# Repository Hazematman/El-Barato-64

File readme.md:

# El Barato 64
Open source N64 development cartridge. Currently a WIP
- Hardware is currently untested
- firmware still needs to be written for board

Uses Altera MAX II EPM570 to emulate N64 cartridge bus. N64 ROM is stored in SDRAM controlled by this FPGA. Uses an STM32 for USB communication and general board control.
This board is designed to be as cheap as possible and beginner friendly. Parts were selected based on their avaliablity in the JLCPCB part inventory. All components except the micro USB connector and reset switch are avalible from JLCPCB, and thus they can manufacture the majority of the board.

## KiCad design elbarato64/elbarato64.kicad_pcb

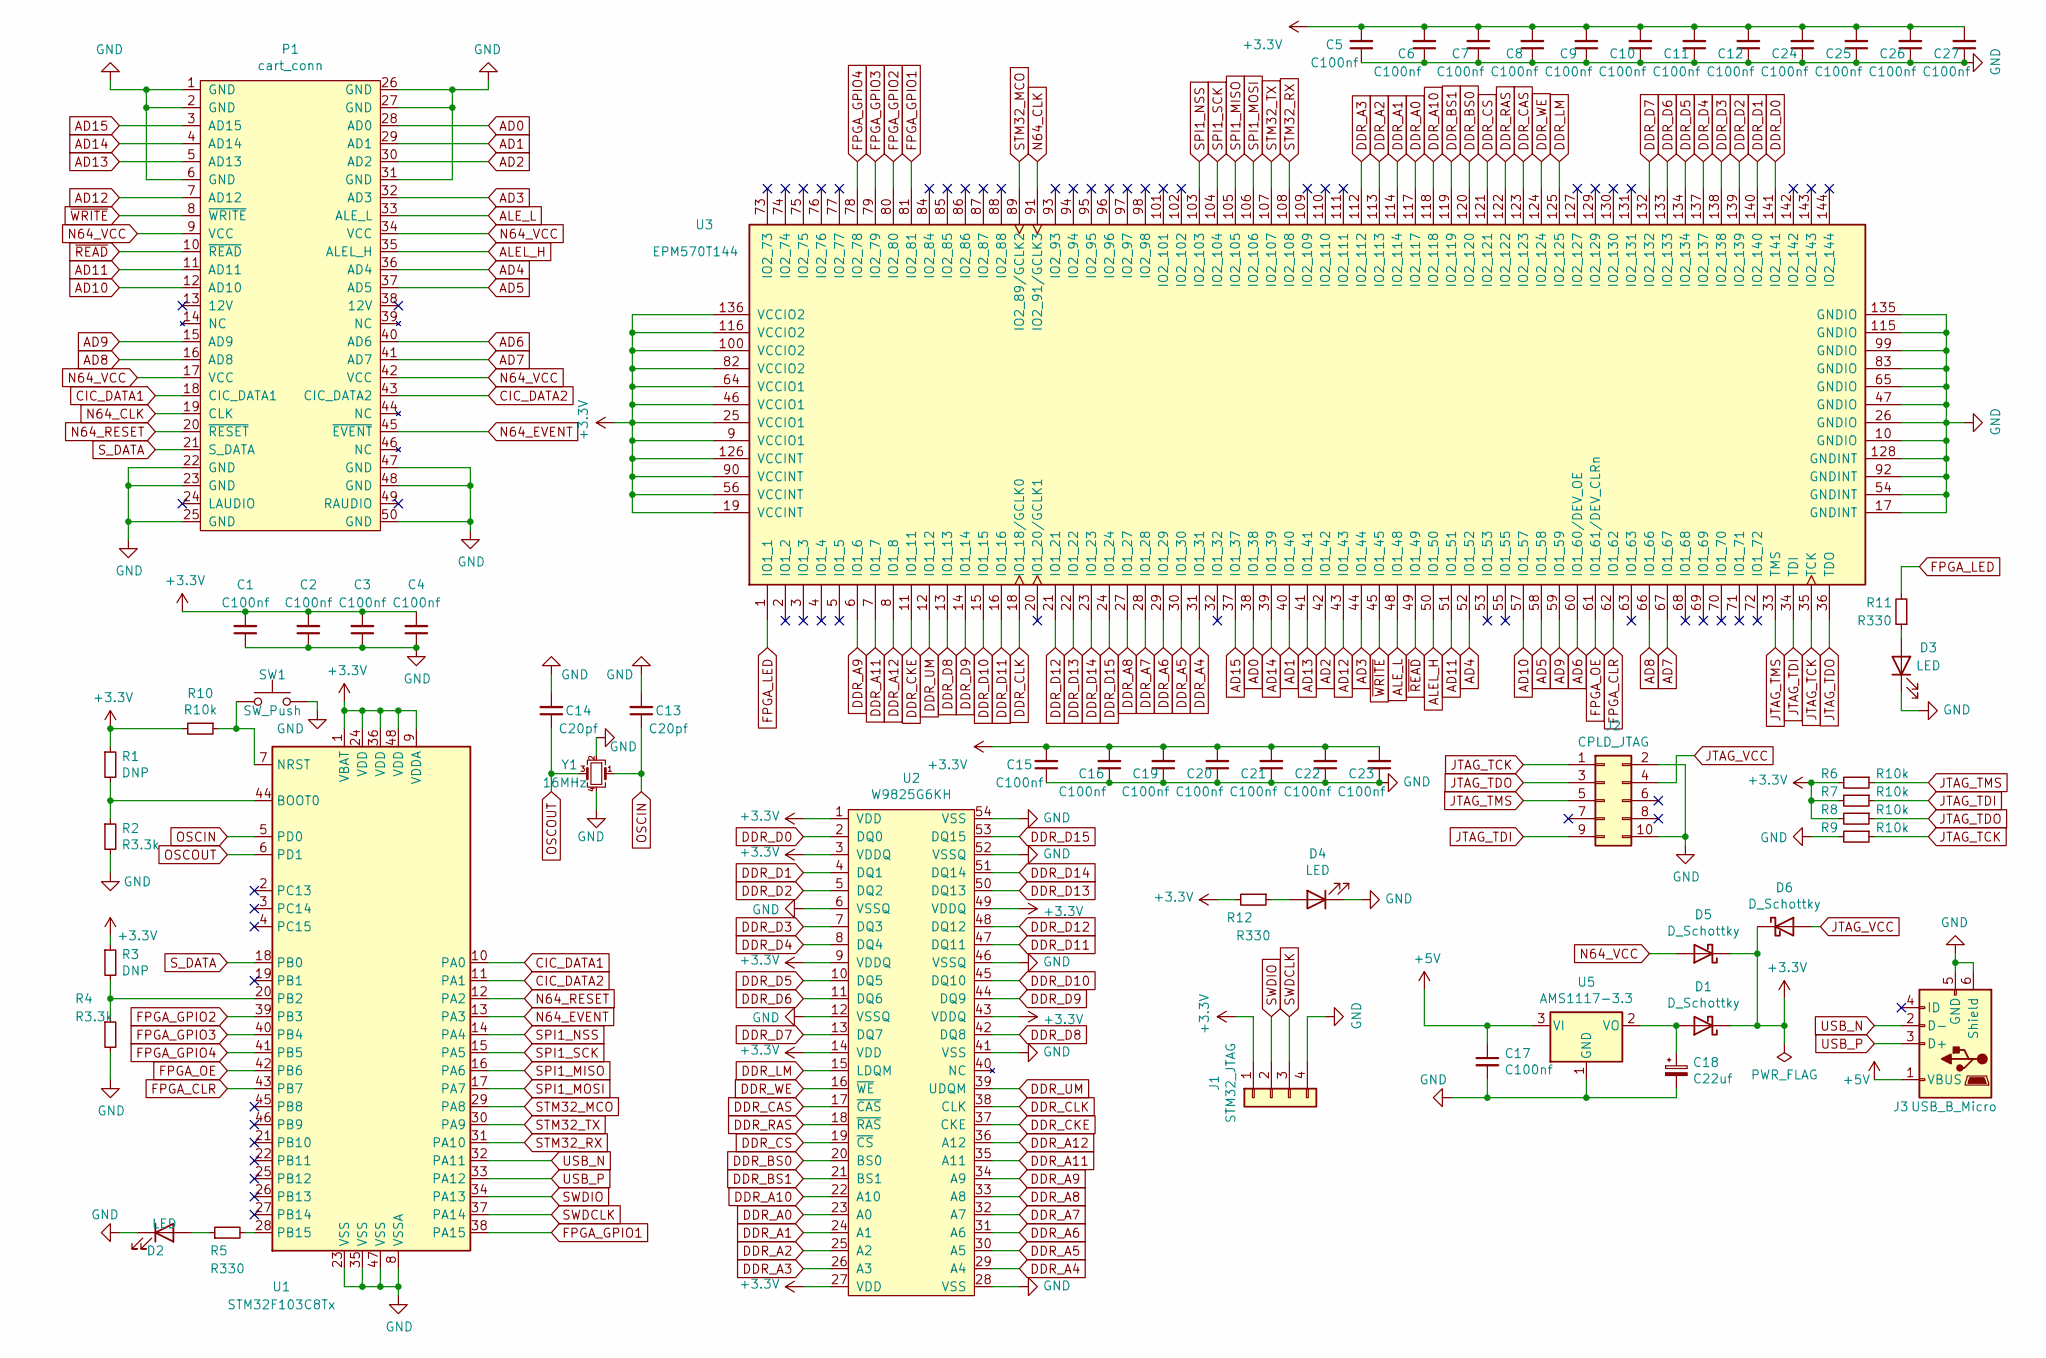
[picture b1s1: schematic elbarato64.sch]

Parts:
C1, C2, C3, C4, C5, C6, C7, C8, C9, C10, C11, C12, C15, C16, C17, C19, C20, C21, C22, C23, C24, C25, C26, C27: C100nf; C_0603_1608Metric_Pad1.05x0.95mm_HandSolder
C13, C14: C20pf; C_0603_1608Metric_Pad1.05x0.95mm_HandSolder
C18: C22uf; C_0603_1608Metric_Pad1.05x0.95mm_HandSolder
D1, D5, D6: D_Schottky; D_SOD-123
D2, D3, D4: LED; LED_0603_1608Metric_Pad1.05x0.95mm_HandSolder
J1: STM32_JTAG; PinHeader_1x04_P2.54mm_Vertical
J2: CPLD_JTAG; PinHeader_2x05_P2.54mm_Vertical
J3: USB_B_Micro; USB_Micro-AB_Molex_47590-0001
P1: cart_conn; Conn_N64
R1, R3: DNP; R_0603_1608Metric_Pad1.05x0.95mm_HandSolder
R2, R4: R3.3k; R_0603_1608Metric_Pad1.05x0.95mm_HandSolder
R5, R11, R12: R330; R_0603_1608Metric_Pad1.05x0.95mm_HandSolder
R6, R7, R8, R9, R10: R10k; R_0603_1608Metric_Pad1.05x0.95mm_HandSolder
SW1: SW_Push; SW_PUSH_6mm
U1: STM32F103C8Tx; LQFP-48_7x7mm_P0.5mm
U2: W9825G6KH; TSOP-II-54_22.2x10.16mm_P0.8mm
U3: EPM570T144; LQFP-144_20x20mm_P0.5mm
U5: AMS1117-3.3; SOT-223-3_TabPin2
Y1: 16MHz; Crystal_SMD_3225-4Pin_3.2x2.5mm_HandSoldering

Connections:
+3V3: C1.2, C2.2, C3.2, C4.2, C5.2, C6.2, C7.2, C8.2, C9.2, C10.2, C11.2, C12.2, C15.2, C16.2, C19.2, C20.2, C21.2, C22.2, C23.2, C24.2, C25.2, C26.2, C27.2, D1.1 (K), D5.1 (K), D6.1 (K), J1.1, R1.1, R3.1, R6.2, R7.2, R8.2, R10.2, R12.2, U1.1 (VBAT), U1.9 (VDDA), U1.24 (VDD), U1.36 (VDD), U1.48 (VDD), U2.1 (VDD), U2.3 (VDDQ), U2.9 (VDDQ), U2.14 (VDD), U2.27 (VDD), U2.43 (VDDQ), U2.49 (VDDQ), U3.9 (VCCIO1), U3.19 (VCCINT), U3.25 (VCCIO1), U3.46 (VCCIO1), U3.56 (VCCINT), U3.64 (VCCIO1), U3.82 (VCCIO2), U3.90 (VCCINT), U3.100 (VCCIO2), U3.116 (VCCIO2), U3.126 (VCCINT), U3.136 (VCCIO2)
+5V: C17.1, J3.1 (VBUS), U5.3 (VI)
AD0: P1.28 (AD0), U3.38 (IO1_38)
AD1: P1.29 (AD1), U3.40 (IO1_40)
AD2: P1.30 (AD2), U3.42 (IO1_42)
AD3: P1.32 (AD3), U3.44 (IO1_44)
AD4: P1.36 (AD4), U3.52 (IO1_52)
AD5: P1.37 (AD5), U3.58 (IO1_58)
AD6: P1.40 (AD6), U3.60 (IO1_60/DEV_OE)
AD7: P1.41 (AD7), U3.67 (IO1_67)
AD8: P1.16 (AD8), U3.66 (IO1_66)
AD9: P1.15 (AD9), U3.59 (IO1_59)
AD10: P1.12 (AD10), U3.57 (IO1_57)
AD11: P1.11 (AD11), U3.51 (IO1_51)
AD12: P1.7 (AD12), U3.43 (IO1_43)
AD13: P1.5 (AD13), U3.41 (IO1_41)
AD14: P1.4 (AD14), U3.39 (IO1_39)
AD15: P1.3 (AD15), U3.37 (IO1_37)
ALEL_H: P1.35 (ALEL_H), U3.50 (IO1_50)
ALE_L: P1.33 (ALE_L), U3.48 (IO1_48)
CIC_DATA1: P1.18 (CIC_DATA1), U1.10 (PA0)
CIC_DATA2: P1.43 (CIC_DATA2), U1.11 (PA1)
DDR_A0: U2.23 (A0), U3.117 (IO2_117)
DDR_A1: U2.24 (A1), U3.114 (IO2_114)
DDR_A2: U2.25 (A2), U3.113 (IO2_113)
DDR_A3: U2.26 (A3), U3.112 (IO2_112)
DDR_A4: U2.29 (A4), U3.31 (IO1_31)
DDR_A5: U2.30 (A5), U3.30 (IO1_30)
DDR_A6: U2.31 (A6), U3.29 (IO1_29)
DDR_A7: U2.32 (A7), U3.28 (IO1_28)
DDR_A8: U2.33 (A8), U3.27 (IO1_27)
DDR_A9: U2.34 (A9), U3.6 (IO1_6)
DDR_A10: U2.22 (A10), U3.118 (IO2_118)
DDR_A11: U2.35 (A11), U3.7 (IO1_7)
DDR_A12: U2.36 (A12), U3.8 (IO1_8)
DDR_BS0: U2.20 (BS0), U3.120 (IO2_120)
DDR_BS1: U2.21 (BS1), U3.119 (IO2_119)
DDR_CAS: U2.17 (~CAS), U3.123 (IO2_123)
DDR_CKE: U2.37 (CKE), U3.11 (IO1_11)
DDR_CLK: U2.38 (CLK), U3.18 (IO1_18/GCLK0)
DDR_CS: U2.19 (~CS), U3.121 (IO2_121)
DDR_D0: U2.2 (DQ0), U3.141 (IO2_141)
DDR_D1: U2.4 (DQ1), U3.140 (IO2_140)
DDR_D2: U2.5 (DQ2), U3.139 (IO2_139)
DDR_D3: U2.7 (DQ3), U3.138 (IO2_138)
DDR_D4: U2.8 (DQ4), U3.137 (IO2_137)
DDR_D5: U2.10 (DQ5), U3.134 (IO2_134)
DDR_D6: U2.11 (DQ6), U3.133 (IO2_133)
DDR_D7: U2.13 (DQ7), U3.132 (IO2_132)
DDR_D8: U2.42 (DQ8), U3.13 (IO1_13)
DDR_D9: U2.44 (DQ9), U3.14 (IO1_14)
DDR_D10: U2.45 (DQ10), U3.15 (IO1_15)
DDR_D11: U2.47 (DQ11), U3.16 (IO1_16)
DDR_D12: U2.48 (DQ12), U3.21 (IO1_21)
DDR_D13: U2.50 (DQ13), U3.22 (IO1_22)
DDR_D14: U2.51 (DQ14), U3.23 (IO1_23)
DDR_D15: U2.53 (DQ15), U3.24 (IO1_24)
DDR_LM: U2.15 (LDQM), U3.125 (IO2_125)
DDR_RAS: U2.18 (~RAS), U3.122 (IO2_122)
DDR_UM: U2.39 (UDQM), U3.12 (IO1_12)
DDR_WE: U2.16 (~WE), U3.124 (IO2_124)
FPGA_CLR: U1.43 (PB7), U3.62 (IO1_62)
FPGA_GPIO1: U1.38 (PA15), U3.81 (IO2_81)
FPGA_GPIO2: U1.39 (PB3), U3.80 (IO2_80)
FPGA_GPIO3: U1.40 (PB4), U3.79 (IO2_79)
FPGA_GPIO4: U1.41 (PB5), U3.78 (IO2_78)
FPGA_LED: R11.2, U3.1 (IO1_1)
FPGA_OE: U1.42 (PB6), U3.61 (IO1_61/DEV_CLRn)
GND: C1.1, C2.1, C3.1, C4.1, C5.1, C6.1, C7.1, C8.1, C9.1, C10.1, C11.1, C12.1, C13.2, C14.2, C15.1, C16.1, C17.2, C18.2, C19.1, C20.1, C21.1, C22.1, C23.1, C24.1, C25.1, C26.1, C27.1, D2.1 (K), D3.1 (K), D4.1 (K), J1.4, J2.2, J2.10, J3.5 (GND), J3.6 (Shield), P1.1 (GND), P1.2 (GND), P1.6 (GND), P1.22 (GND), P1.23 (GND), P1.25 (GND), P1.26 (GND), P1.27 (GND), P1.31 (GND), P1.47 (GND), P1.48 (GND), P1.50 (GND), R2.2, R4.2, R9.2, SW1.2, U1.8 (VSSA), U1.23 (VSS), U1.35 (VSS), U1.47 (VSS), U2.6 (VSSQ), U2.12 (VSSQ), U2.28 (VSS), U2.41 (VSS), U2.46 (VSSQ), U2.52 (VSSQ), U2.54 (VSS), U3.10 (GNDIO), U3.17 (GNDINT), U3.26 (GNDIO), U3.47 (GNDIO), U3.54 (GNDINT), U3.65 (GNDIO), U3.83 (GNDIO), U3.92 (GNDINT), U3.99 (GNDIO), U3.115 (GNDIO), U3.128 (GNDINT), U3.135 (GNDIO), U5.1 (GND), Y1.2, Y1.4
JTAG_TCK: J2.1, R9.1, U3.35 (TCK)
JTAG_TDI: J2.9, R7.1, U3.34 (TDI)
JTAG_TDO: J2.3, R8.1, U3.36 (TDO)
JTAG_TMS: J2.5, R6.1, U3.33 (TMS)
JTAG_VCC: D6.2 (A), J2.4
N64_CLK: P1.19 (CLK), U3.91 (IO2_91/GCLK3)
N64_EVENT: P1.45 (~EVENT), U1.13 (PA3)
N64_RESET: P1.20 (~RESET), U1.12 (PA2)
N64_VCC: D5.2 (A), P1.9 (VCC), P1.17 (VCC), P1.34 (VCC), P1.42 (VCC)
unnamed: C18.1, D1.2 (A), U5.2 (VO)
unnamed: D2.2 (A), R5.1
unnamed: D3.2 (A), R11.1
unnamed: D4.2 (A), R12.1
unnamed: R1.2, R2.1, U1.44 (BOOT0)
unnamed: R3.2, R4.1, U1.20 (PB2)
unnamed: R5.2, U1.28 (PB15)
unnamed: R10.1, SW1.1, U1.7 (NRST)
OSCIN: C13.1, U1.5 (PD0), Y1.1
OSCOUT: C14.1, U1.6 (PD1), Y1.3
SPI1_MISO: U1.16 (PA6), U3.105 (IO2_105)
SPI1_MOSI: U1.17 (PA7), U3.106 (IO2_106)
SPI1_NSS: U1.14 (PA4), U3.103 (IO2_103)
SPI1_SCK: U1.15 (PA5), U3.104 (IO2_104)
STM32_MCO: U1.29 (PA8), U3.89 (IO2_89/GCLK2)
STM32_RX: U1.31 (PA10), U3.108 (IO2_108)
STM32_TX: U1.30 (PA9), U3.107 (IO2_107)
SWDCLK: J1.3, U1.37 (PA14)
SWDIO: J1.2, U1.34 (PA13)
S_DATA: P1.21 (S_DATA), U1.18 (PB0)
USB_N: J3.2 (D-), U1.32 (PA11)
USB_P: J3.3 (D+), U1.33 (PA12)
~READ: P1.10 (~READ), U3.49 (IO1_49)
~WRITE: P1.8 (~WRITE), U3.45 (IO1_45)

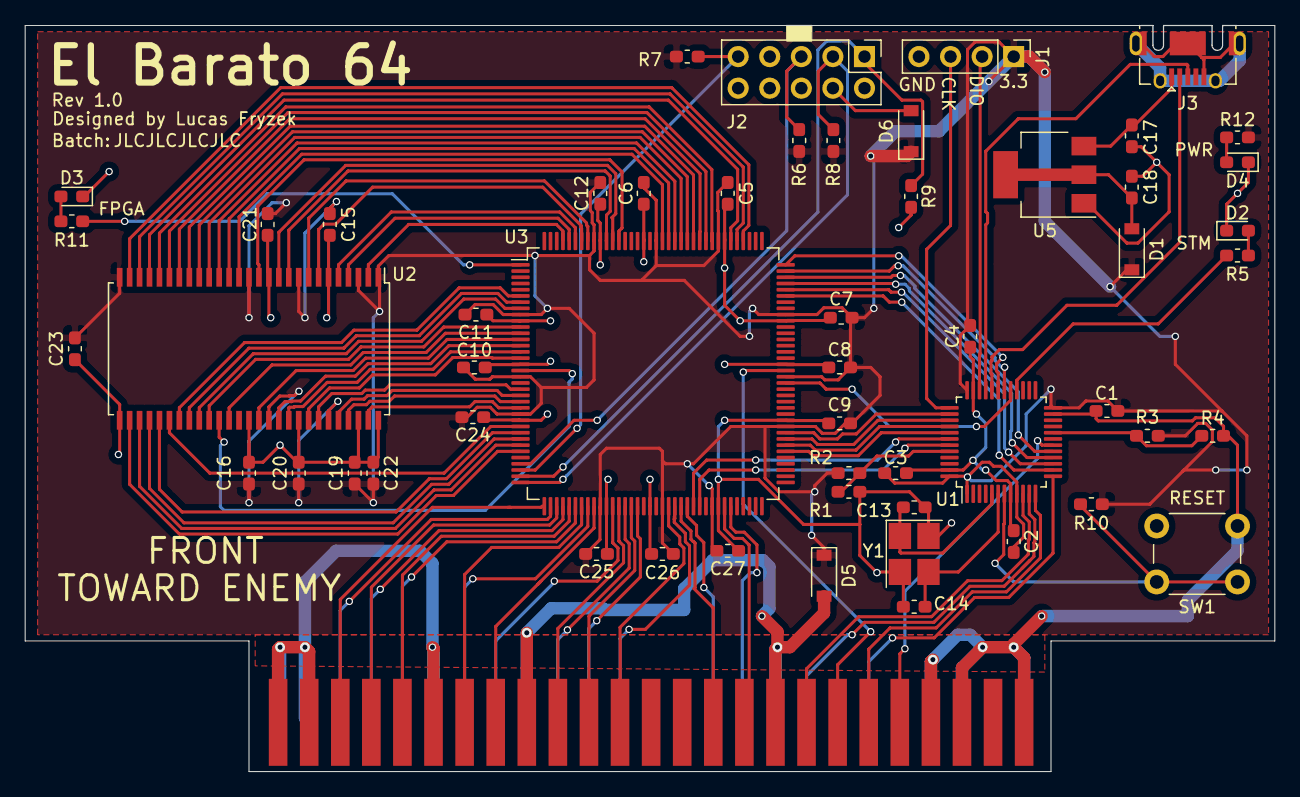
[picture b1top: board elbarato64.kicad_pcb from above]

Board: 2 copper layers, 100.5 x 60.0 mm, 55 parts (0 on the bottom side), 102 nets.

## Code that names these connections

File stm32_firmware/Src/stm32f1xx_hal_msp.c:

/* USER CODE BEGIN Header */
/**
  ******************************************************************************
  * File Name          : stm32f1xx_hal_msp.c
  * Description        : This file provides code for the MSP Initialization 
  *                      and de-Initialization codes.
  ******************************************************************************
  * @attention
  *
  * <h2><center>&copy; Copyright (c) 2020 STMicroelectronics.
  * All rights reserved.</center></h2>
  *
  * This software component is licensed by ST under BSD 3-Clause license,
  * the "License"; You may not use this file except in compliance with the
  * License. You may obtain a copy of the License at:
  *                        opensource.org/licenses/BSD-3-Clause
  *
  ******************************************************************************
  */
/* USER CODE END Header */

/* Includes ------------------------------------------------------------------*/
#include "main.h"
/* USER CODE BEGIN Includes */

/* USER CODE END Includes */

/* Private typedef -----------------------------------------------------------*/
/* USER CODE BEGIN TD */

/* USER CODE END TD */

/* Private define ------------------------------------------------------------*/
/* USER CODE BEGIN Define */
 
/* USER CODE END Define */

/* Private macro -------------------------------------------------------------*/
/* USER CODE BEGIN Macro */

/* USER CODE END Macro */

/* Private variables ---------------------------------------------------------*/
/* USER CODE BEGIN PV */

/* USER CODE END PV */

/* Private function prototypes -----------------------------------------------*/
/* USER CODE BEGIN PFP */

/* USER CODE END PFP */

/* External functions --------------------------------------------------------*/
/* USER CODE BEGIN ExternalFunctions */

/* USER CODE END ExternalFunctions */

/* USER CODE BEGIN 0 */

/* USER CODE END 0 */
/**
  * Initializes the Global MSP.
  */
void HAL_MspInit(void)
{
  /* USER CODE BEGIN MspInit 0 */

  /* USER CODE END MspInit 0 */

  __HAL_RCC_AFIO_CLK_ENABLE();
  __HAL_RCC_PWR_CLK_ENABLE();

  /* System interrupt init*/

  /** DISABLE: JTAG-DP Disabled and SW-DP Disabled 
  */
  __HAL_AFIO_REMAP_SWJ_DISABLE();

  /* USER CODE BEGIN MspInit 1 */

  /* USER CODE END MspInit 1 */
}

/**
* @brief SPI MSP Initialization
* This function configures the hardware resources used in this example
* @param hspi: SPI handle pointer
* @retval None
*/
void HAL_SPI_MspInit(SPI_HandleTypeDef* hspi)
{
  GPIO_InitTypeDef GPIO_InitStruct = {0};
  if(hspi->Instance==SPI1)
  {
  /* USER CODE BEGIN SPI1_MspInit 0 */

  /* USER CODE END SPI1_MspInit 0 */
    /* Peripheral clock enable */
    __HAL_RCC_SPI1_CLK_ENABLE();
  
    __HAL_RCC_GPIOA_CLK_ENABLE();
    /**SPI1 GPIO Configuration    
    PA5     ------> SPI1_SCK
    PA6     ------> SPI1_MISO
    PA7     ------> SPI1_MOSI 
    */
    GPIO_InitStruct.Pin = GPIO_PIN_5|GPIO_PIN_7;
    GPIO_InitStruct.Mode = GPIO_MODE_AF_PP;
    GPIO_InitStruct.Speed = GPIO_SPEED_FREQ_HIGH;
    HAL_GPIO_Init(GPIOA, &GPIO_InitStruct);

    GPIO_InitStruct.Pin = GPIO_PIN_6;
    GPIO_InitStruct.Mode = GPIO_MODE_INPUT;
    GPIO_InitStruct.Pull = GPIO_NOPULL;
    HAL_GPIO_Init(GPIOA, &GPIO_InitStruct);

  /* USER CODE BEGIN SPI1_MspInit 1 */

  /* USER CODE END SPI1_MspInit 1 */
  }

}

/**
* @brief SPI MSP De-Initialization
* This function freeze the hardware resources used in this example
* @param hspi: SPI handle pointer
* @retval None
*/
void HAL_SPI_MspDeInit(SPI_HandleTypeDef* hspi)
{
  if(hspi->Instance==SPI1)
  {
  /* USER CODE BEGIN SPI1_MspDeInit 0 */

  /* USER CODE END SPI1_MspDeInit 0 */
    /* Peripheral clock disable */
    __HAL_RCC_SPI1_CLK_DISABLE();
  
    /**SPI1 GPIO Configuration    
    PA5     ------> SPI1_SCK
    PA6     ------> SPI1_MISO
    PA7     ------> SPI1_MOSI 
    */
    HAL_GPIO_DeInit(GPIOA, GPIO_PIN_5|GPIO_PIN_6|GPIO_PIN_7);

  /* USER CODE BEGIN SPI1_MspDeInit 1 */

  /* USER CODE END SPI1_MspDeInit 1 */
  }

}

/**
* @brief UART MSP Initialization
* This function configures the hardware resources used in this example
* @param huart: UART handle pointer
* @retval None
*/
void HAL_UART_MspInit(UART_HandleTypeDef* huart)
{
  GPIO_InitTypeDef GPIO_InitStruct = {0};
  if(huart->Instance==USART1)
  {
  /* USER CODE BEGIN USART1_MspInit 0 */

  /* USER CODE END USART1_MspInit 0 */
    /* Peripheral clock enable */
    __HAL_RCC_USART1_CLK_ENABLE();
  
    __HAL_RCC_GPIOA_CLK_ENABLE();
    /**USART1 GPIO Configuration    
    PA9     ------> USART1_TX
    PA10     ------> USART1_RX 
    */
    GPIO_InitStruct.Pin = GPIO_PIN_9;
    GPIO_InitStruct.Mode = GPIO_MODE_AF_PP;
    GPIO_InitStruct.Speed = GPIO_SPEED_FREQ_HIGH;
    HAL_GPIO_Init(GPIOA, &GPIO_InitStruct);

    GPIO_InitStruct.Pin = GPIO_PIN_10;
    GPIO_InitStruct.Mode = GPIO_MODE_INPUT;
    GPIO_InitStruct.Pull = GPIO_NOPULL;
    HAL_GPIO_Init(GPIOA, &GPIO_InitStruct);

  /* USER CODE BEGIN USART1_MspInit 1 */

  /* USER CODE END USART1_MspInit 1 */
  }

}

/**
* @brief UART MSP De-Initialization
* This function freeze the hardware resources used in this example
* @param huart: UART handle pointer
* @retval None
*/
void HAL_UART_MspDeInit(UART_HandleTypeDef* huart)
{
  if(huart->Instance==USART1)
  {
  /* USER CODE BEGIN USART1_MspDeInit 0 */

  /* USER CODE END USART1_MspDeInit 0 */
    /* Peripheral clock disable */
    __HAL_RCC_USART1_CLK_DISABLE();
  
    /**USART1 GPIO Configuration    
    PA9     ------> USART1_TX
    PA10     ------> USART1_RX 
    */
    HAL_GPIO_DeInit(GPIOA, GPIO_PIN_9|GPIO_PIN_10);

  /* USER CODE BEGIN USART1_MspDeInit 1 */

  /* USER CODE END USART1_MspDeInit 1 */
  }

}

/* USER CODE BEGIN 1 */

/* USER CODE END 1 */

/************************ (C) COPYRIGHT STMicroelectronics *****END OF FILE****/

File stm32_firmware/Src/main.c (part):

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  /*Configure GPIO pin Output Level */
  HAL_GPIO_WritePin(GPIOB, GPIO_PIN_15, GPIO_PIN_RESET);

  /*Configure GPIO pin : PA0 */
  GPIO_InitStruct.Pin = GPIO_PIN_0;
  GPIO_InitStruct.Mode = GPIO_MODE_INPUT;
  GPIO_InitStruct.Pull = GPIO_NOPULL;
  GPIO_InitStruct.Speed = GPIO_SPEED_FREQ_MEDIUM;
  HAL_GPIO_Init(GPIOA, &GPIO_InitStruct);

  /*Configure GPIO pin : PA1 */
  GPIO_InitStruct.Pin = GPIO_PIN_1;
  GPIO_InitStruct.Mode = GPIO_MODE_INPUT;
  GPIO_InitStruct.Pull = GPIO_NOPULL;
  GPIO_InitStruct.Speed = GPIO_SPEED_FREQ_MEDIUM;
  HAL_GPIO_Init(GPIOA, &GPIO_InitStruct);

  /*Configure GPIO pin : PA4 */
  GPIO_InitStruct.Pin = GPIO_PIN_4;
  GPIO_InitStruct.Mode = GPIO_MODE_OUTPUT_PP;
  GPIO_InitStruct.Pull = GPIO_NOPULL;
  GPIO_InitStruct.Speed = GPIO_SPEED_FREQ_LOW;
  HAL_GPIO_Init(GPIOA, &GPIO_InitStruct);

  /*Configure GPIO pin : PB15 */
  GPIO_InitStruct.Pin = GPIO_PIN_15;
  GPIO_InitStruct.Mode = GPIO_MODE_OUTPUT_PP;
  GPIO_InitStruct.Pull = GPIO_NOPULL;
  GPIO_InitStruct.Speed = GPIO_SPEED_FREQ_LOW;
  HAL_GPIO_Init(GPIOB, &GPIO_InitStruct);

  /*Configure GPIO pin : PA8 */
  GPIO_InitStruct.Pin = GPIO_PIN_8;
  GPIO_InitStruct.Mode = GPIO_MODE_AF_PP;
  GPIO_InitStruct.Speed = GPIO_SPEED_FREQ_LOW;
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
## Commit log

2020-07-05 Inital commit
2020-07-05 Update readme.md
    Fix typo
2020-07-22 remove unused files
2020-07-23 Add inital verilog code for max 2
2020-07-23 Add inital verilog test file
2020-07-23 Update test to verify spi read and write
2020-07-24 Add quartus project
2020-08-02 Update SPI controller to be stable
2020-08-03 Add stm32 firmware
2020-08-10 Add n64 bus logic
    Implement n64 bus logic system verilog file and unit test case for it.
    Needs to be intergrated into state_controller.
2020-08-11 Add serial programmer and various fixes
